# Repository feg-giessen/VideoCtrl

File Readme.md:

# VideoController

Some more photos: https://www.flickr.com/photos/peschuster/tags/videoctrl/

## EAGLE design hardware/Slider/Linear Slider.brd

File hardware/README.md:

# Hardware Files #

- schematics
- part lists
- board layouts

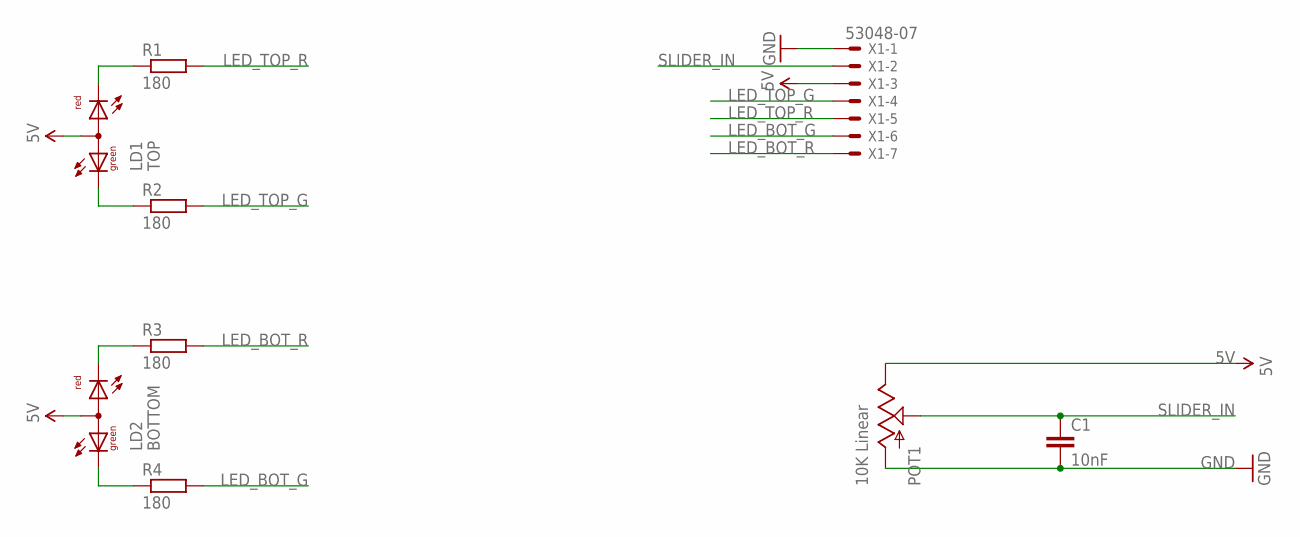
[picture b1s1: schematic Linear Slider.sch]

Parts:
C1: 10nF; 0603-CAP
LD1: TOP; DUOLED-A-5MM
LD2: BOTTOM; DUOLED-A-5MM
POT1: 10K Linear; SLIDER60
R1, R2, R3, R4: 180; R0603
X1: 53048-07

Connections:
5V: LD1.A, LD2.A, POT1.1 (E), X1.3
GND: C1.2, POT1.3 (A), X1.1
LED_BOT_G: R4.2, X1.6
LED_BOT_R: R3.2, X1.7
LED_TOP_G: R2.2, X1.4
LED_TOP_R: R1.2, X1.5
unnamed: LD1.CR, R1.1
unnamed: LD1.CX (CG), R2.1
unnamed: LD2.CX (CG), R4.1
unnamed: LD2.CR, R3.1
SLIDER_IN: C1.1, POT1.2A (S), X1.2

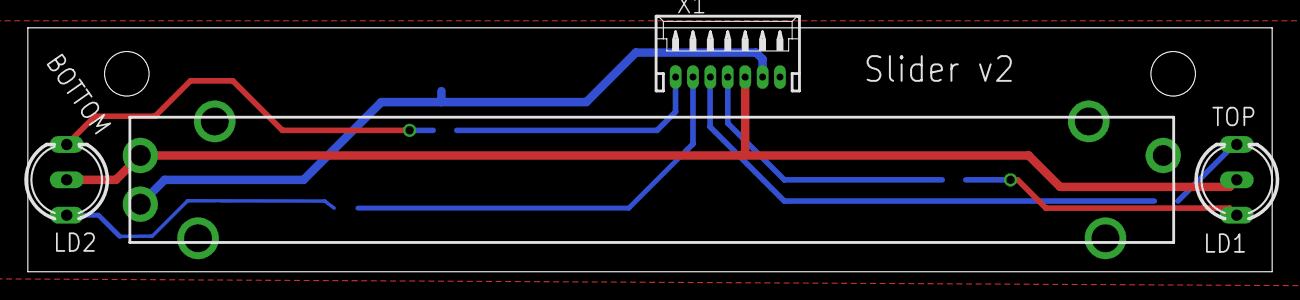
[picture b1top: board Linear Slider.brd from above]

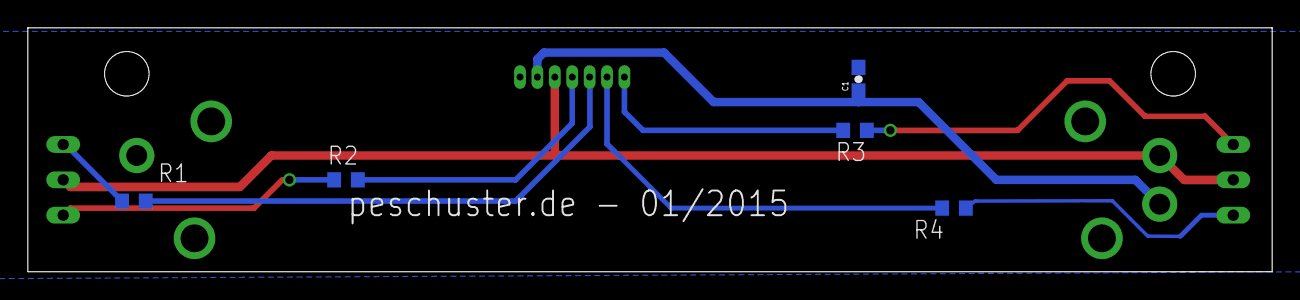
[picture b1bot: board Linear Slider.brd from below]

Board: 2 copper layers, 89.4 x 17.5 mm, 9 parts (5 on the bottom side), 11 nets.

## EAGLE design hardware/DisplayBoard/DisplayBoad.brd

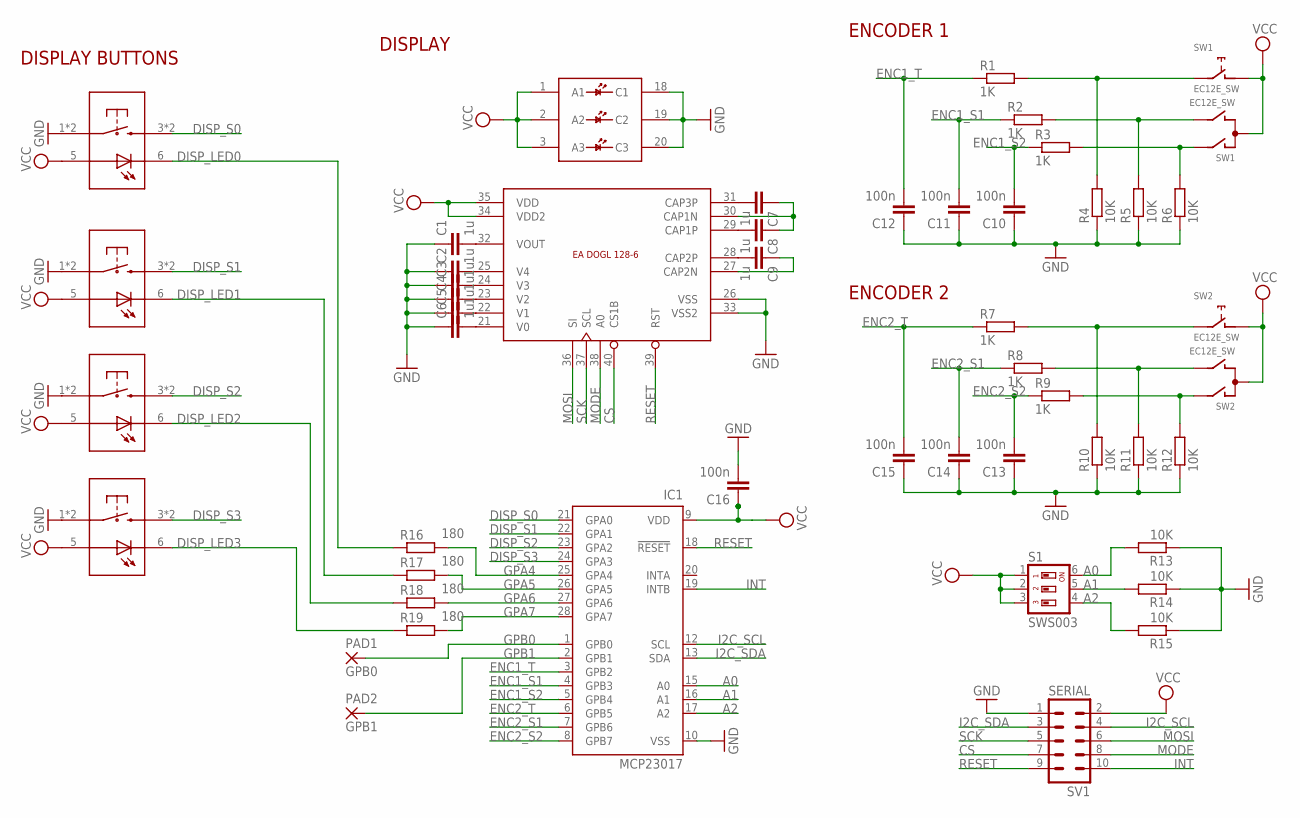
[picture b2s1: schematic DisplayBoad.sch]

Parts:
C1, C2, C3, C4, C5, C6, C7, C8, C9: 1u; C0805
C10, C11, C12, C13, C14, C15, C16: 100n; C0603
IC1: MCP23017; SSOP28
PAD1: GPB0; 2,15/1,0
PAD2: GPB1; 2,15/1,0
R1, R2, R3, R7, R8, R9: 1K; R0603
R4, R5, R6, R10, R11, R12, R13, R14, R15: 10K; R0603
R16, R17, R18, R19: 180; R0603
S1: SWS003; SMS-003
SV1: SERIAL; MA05-2
SW1, SW2: EC12E_SW; ALPS_EC12E_SW
U1: EADOGL128-62; EA_DOGL128-6
U$2, U$3, U$4, U$5: LP15

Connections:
A0: IC1.15 (A0), R13.2, S1.6
A1: IC1.16 (A1), R14.2, S1.5
A2: IC1.17 (A2), R15.2, S1.4
CS: SV1.7, U1.40 (CS1B)
DISP_LED0: R16.1, U$2.6
DISP_LED1: R17.1, U$3.6
DISP_LED2: R18.1, U$4.6
DISP_LED3: R19.1, U$5.6
DISP_S0: IC1.21 (GPA0), U$2.3, U$2.4 (3)
DISP_S1: IC1.22 (GPA1), U$3.3, U$3.4 (3)
DISP_S2: IC1.23 (GPA2), U$4.3, U$4.4 (3)
DISP_S3: IC1.24 (GPA3), U$5.3, U$5.4 (3)
ENC1_S1: C11.2, IC1.4 (GPB3), R2.1
ENC1_S2: C10.2, IC1.5 (GPB4), R3.1
ENC1_T: C12.2, IC1.3 (GPB2), R1.1
ENC2_S1: C14.2, IC1.7 (GPB6), R8.1
ENC2_S2: C13.2, IC1.8 (GPB7), R9.1
ENC2_T: C15.2, IC1.6 (GPB5), R7.1
GND: C1.1, C2.1, C3.1, C4.1, C5.1, C6.1, C10.1, C11.1, C12.1, C13.1, C14.1, C15.1, C16.2, IC1.10 (VSS), R4.1, R5.1, R6.1, R10.1, R11.1, R12.1, R13.1, R14.1, R15.1, SV1.1, U1.18 (C1), U1.19 (C2), U1.20 (C3), U1.26 (VSS), U1.33 (VSS2), U$2.1, U$2.2 (1), U$3.1, U$3.2 (1), U$4.1, U$4.2 (1), U$5.1, U$5.2 (1)
GPA4: IC1.25 (GPA4), R16.2
GPA5: IC1.26 (GPA5), R17.2
GPA6: IC1.27 (GPA6), R18.2
GPA7: IC1.28 (GPA7), R19.2
GPB0: IC1.1 (GPB0), PAD1.1
GPB1: IC1.2 (GPB1), PAD2.1
I2C_SCL: IC1.12 (SCL), SV1.4
I2C_SDA: IC1.13 (SDA), SV1.3
INT: IC1.19 (INTB), SV1.10
MODE: SV1.8, U1.38 (A0)
MOSI: SV1.6, U1.36 (SI)
unnamed: C1.2, U1.32 (VOUT)
unnamed: C2.2, U1.25 (V4)
unnamed: C3.2, U1.24 (V3)
unnamed: C4.2, U1.23 (V2)
unnamed: C5.2, U1.22 (V1)
unnamed: C6.2, U1.21 (V0)
unnamed: C7.2, U1.31 (CAP3P)
unnamed: C8.2, U1.29 (CAP1P)
unnamed: C9.2, U1.28 (CAP2P)
unnamed: C9.1, U1.27 (CAP2N)
unnamed: C7.1, C8.1, U1.30 (CAP1N)
unnamed: R7.2, R10.2, SW2.E (2)
unnamed: R8.2, R11.2, SW2.B
unnamed: R9.2, R12.2, SW2.A
unnamed: R1.2, R4.2, SW1.E (2)
unnamed: R2.2, R5.2, SW1.B
unnamed: R3.2, R6.2, SW1.A
RESET: IC1.18 (!RESET), SV1.9, U1.39 (RST)
SCK: SV1.5, U1.37 (SCL)
VCC: C16.1, IC1.9 (VDD), S1.1, S1.2, S1.3, SV1.2, SW1.C, SW1.D (1), SW2.C, SW2.D (1), U1.1 (A1), U1.2 (A2), U1.3 (A3), U1.34 (VDD2), U1.35 (VDD), U$2.5, U$3.5, U$4.5, U$5.5

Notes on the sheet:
ENCODER 1
ENCODER 2
DISPLAY BUTTONS
DISPLAY

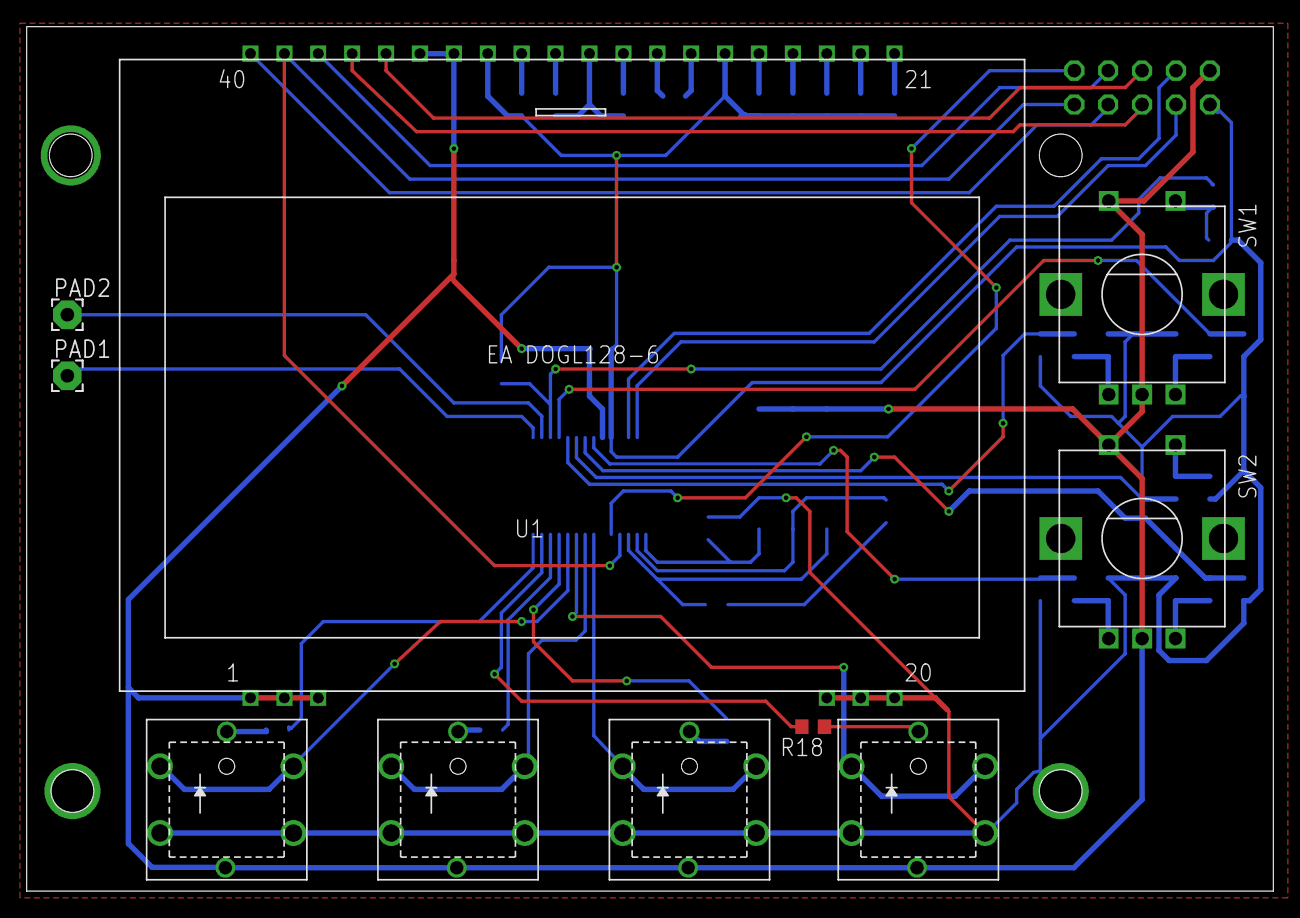
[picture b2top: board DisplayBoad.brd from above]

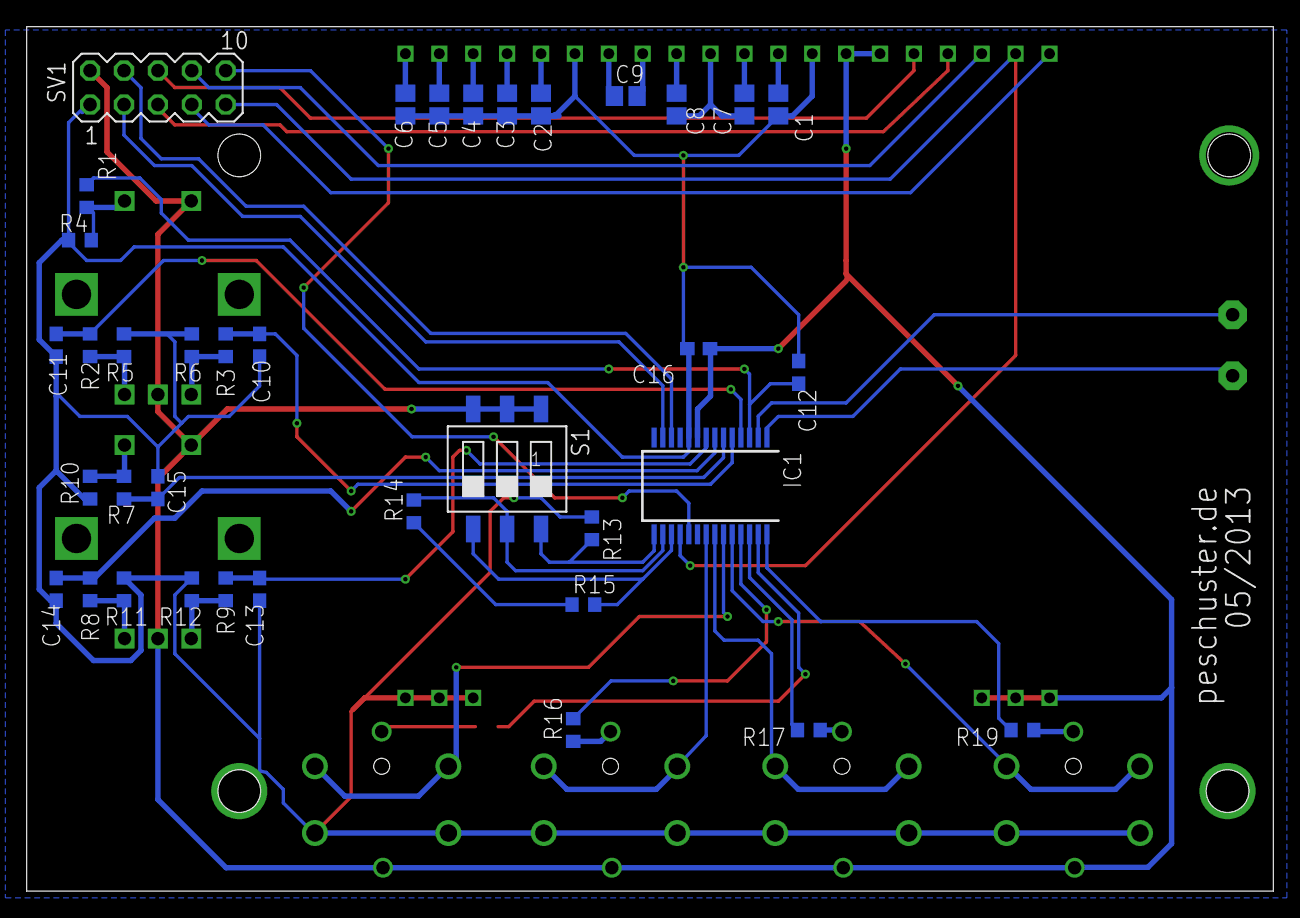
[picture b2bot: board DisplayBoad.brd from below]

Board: 2 copper layers, 93.4 x 64.8 mm, 47 parts (37 on the bottom side), 50 nets.

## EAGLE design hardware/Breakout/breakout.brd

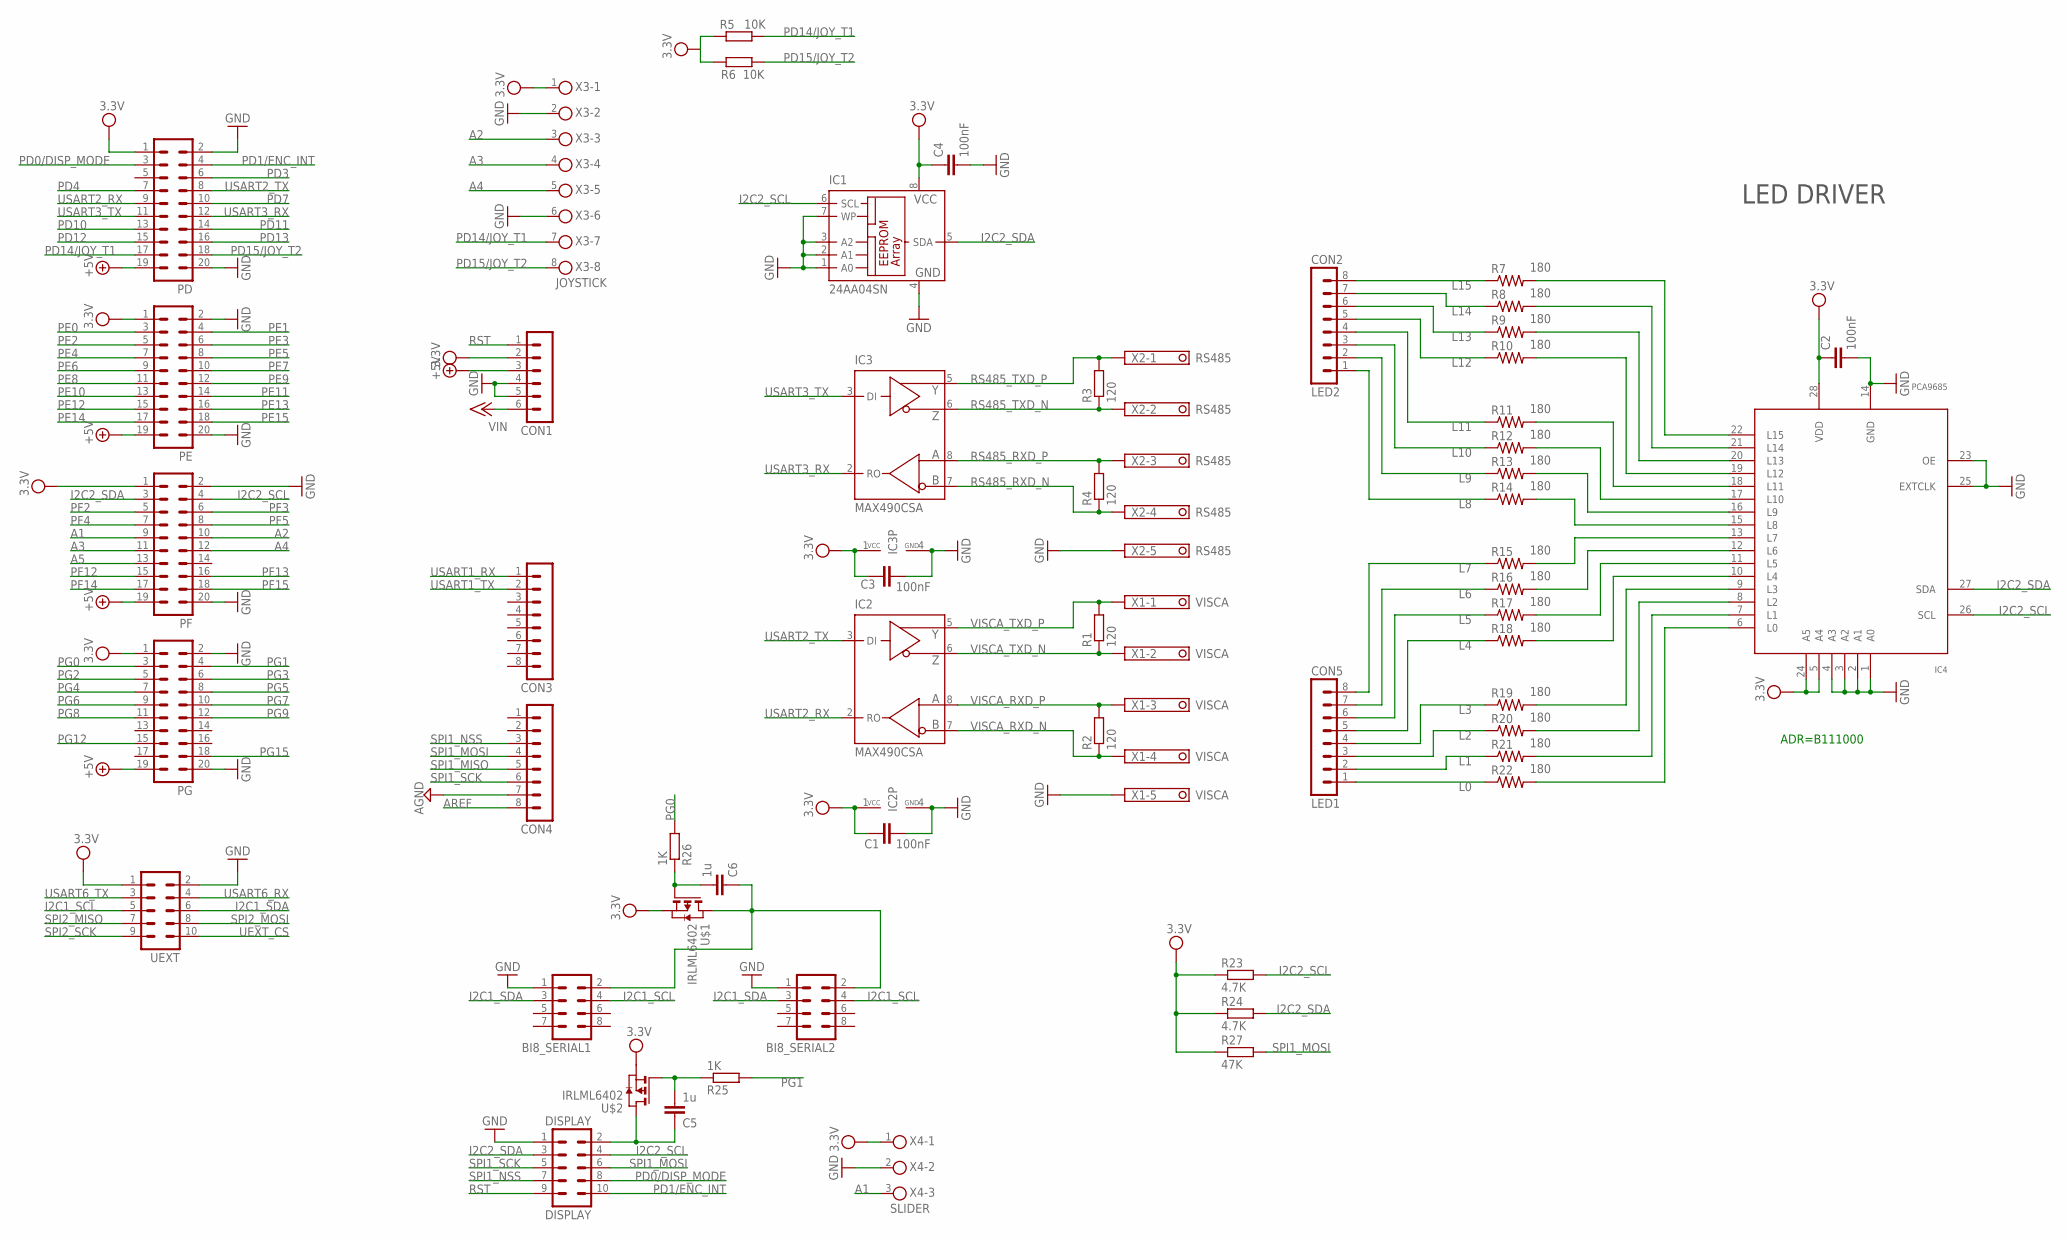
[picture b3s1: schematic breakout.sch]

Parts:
BI8_SERIAL1, BI8_SERIAL2: MA04-2
C1, C2, C3, C4: 100nF; 0603-CAP
C5, C6: 1u; C0805
CON1: MA06-1
CON2: LED2; MA08-1
CON3, CON4: MA08-1
CON5: LED1; MA08-1
DISPLAY: DISPLAY; MA05-2
IC1: 24AA04SN; SO-08
IC2, IC3: MAX490CSA; SO08
IC4: PCA9685; TSSOP28
PD: MA10-2
PE: MA10-2
PF: MA10-2
PG: MA10-2
R1, R2, R3, R4: 120; R0603
R5, R6: 10K; R0603
R7, R8, R9, R10, R11, R12, R13, R14, R15, R16, R17, R18, R19, R20, R21, R22: 180; 0603-RES
R23, R24: 4.7K; R0603
R25, R26: 1K; R0603
R27: 47K; R0603
U$1, U$2: IRLML6402; SOT-23
UEXT: ML10L
X1: VISCA; 1751277
X2: RS485; 1751277
X3: JOYSTICK; 8POL35
X4: SLIDER; 3POL35

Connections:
+5V: CON1.3, PD.19, PE.19, PF.19, PG.19
A1: PF.9, X4.3
A2: PF.10, X3.3
A3: PF.11, X3.4
A4: PF.12, X3.5
A5: PF.13
AGND: CON4.7
AREF: CON4.8
GND: BI8_SERIAL1.1, BI8_SERIAL2.1, C1.2, C2.2, C3.2, C4.2, CON1.4, CON1.5, DISPLAY.1, IC1.1 (A0), IC1.2 (A1), IC1.3 (A2), IC1.4 (GND), IC1.7 (WP), IC2.4 (GND), IC3.4 (GND), IC4.1 (A0), IC4.2 (A1), IC4.3 (A2), IC4.4 (A3), IC4.14 (GND), IC4.23 (OE), IC4.25 (EXTCLK), PD.2, PD.20, PE.2, PE.20, PF.2, PF.20, PG.2, PG.20, UEXT.2, X1.5, X2.5, X3.2, X3.6, X4.2
I2C1_SCL: BI8_SERIAL1.4, BI8_SERIAL2.4, UEXT.5
I2C1_SDA: BI8_SERIAL1.3, BI8_SERIAL2.3, UEXT.6
I2C2_SCL: DISPLAY.4, IC1.6 (SCL), IC4.26 (SCL), PF.4, R23.2
I2C2_SDA: DISPLAY.3, IC1.5 (SDA), IC4.27 (SDA), PF.3, R24.2
L0: CON5.1, R22.1
L1: CON5.2, R21.1
L2: CON5.3, R20.1
L3: CON5.4, R19.1
L4: CON5.5, R18.1
L5: CON5.6, R17.1
L6: CON5.7, R16.1
L7: CON5.8, R15.1
L8: CON2.1, R14.1
L9: CON2.2, R13.1
L10: CON2.3, R12.1
L11: CON2.4, R11.1
L12: CON2.5, R10.1
L13: CON2.6, R9.1
L14: CON2.7, R8.1
L15: CON2.8, R7.1
unnamed: C5.2, R25.1, U$2.1 (G)
unnamed: IC4.13 (L7), R15.2
unnamed: IC4.12 (L6), R16.2
unnamed: C6.2, R26.1, U$1.1 (G)
unnamed: IC4.11 (L5), R17.2
unnamed: BI8_SERIAL1.2, BI8_SERIAL2.2, C6.1, U$1.3 (D)
unnamed: IC4.10 (L4), R18.2
unnamed: IC4.9 (L3), R19.2
unnamed: IC4.8 (L2), R20.2
unnamed: IC4.7 (L1), R21.2
unnamed: C5.1, DISPLAY.2, U$2.3 (D)
unnamed: IC4.6 (L0), R22.2
unnamed: IC4.15 (L8), R14.2
unnamed: IC4.16 (L9), R13.2
unnamed: IC4.17 (L10), R12.2
unnamed: IC4.18 (L11), R11.2
unnamed: IC4.19 (L12), R10.2
unnamed: IC4.20 (L13), R9.2
unnamed: IC4.21 (L14), R8.2
unnamed: IC4.22 (L15), R7.2
PD0/DISP_MODE: DISPLAY.8, PD.3
PD1/ENC_INT: DISPLAY.10, PD.4
PD3: PD.6
PD4: PD.7
PD7: PD.10
PD10: PD.13
PD11: PD.14
PD12: PD.15
PD13: PD.16
PD14/JOY_T1: PD.17, R5.2, X3.7
PD15/JOY_T2: PD.18, R6.2, X3.8
PE0: PE.3
PE1: PE.4
PE2: PE.5
PE3: PE.6
PE4: PE.7
PE5: PE.8
PE6: PE.9
PE7: PE.10
PE8: PE.11
PE9: PE.12
PE10: PE.13
PE11: PE.14
PE12: PE.15
PE13: PE.16
PE14: PE.17
PE15: PE.18
PF2: PF.5
PF3: PF.6
PF4: PF.7
PF5: PF.8
PF12: PF.15
PF13: PF.16
PF14: PF.17
PF15: PF.18
PG0: PG.3, R26.2
PG1: PG.4, R25.2
PG2: PG.5
PG3: PG.6
PG4: PG.7
PG5: PG.8
PG6: PG.9
PG7: PG.10
PG8: PG.11
PG9: PG.12
PG12: PG.15
PG15: PG.18
RS485_RXD_N: IC3.7 (B), R4.1, X2.4
RS485_RXD_P: IC3.8 (A), R4.2, X2.3
RS485_TXD_N: IC3.6 (Z), R3.1, X2.2
RS485_TXD_P: IC3.5 (Y), R3.2, X2.1
RST: CON1.1, DISPLAY.9
SPI1_MISO: CON4.5
SPI1_MOSI: CON4.4, DISPLAY.6, R27.2
SPI1_NSS: CON4.3, DISPLAY.7
SPI1_SCK: CON4.6, DISPLAY.5
SPI2_MISO: UEXT.7
SPI2_MOSI: UEXT.8
SPI2_SCK: UEXT.9
UEXT_CS: UEXT.10
USART1_RX: CON3.1
USART1_TX: CON3.2
USART2_RX: IC2.2 (RO), PD.9
USART2_TX: IC2.3 (DI), PD.8
USART3_RX: IC3.2 (RO), PD.12
USART3_TX: IC3.3 (DI), PD.11
USART6_RX: UEXT.4
USART6_TX: UEXT.3
VCC: C1.1, C2.1, C3.1, C4.1, CON1.2, IC1.8 (VCC), IC2.1 (VCC), IC3.1 (VCC), IC4.5 (A4), IC4.24 (A5), IC4.28 (VDD), PD.1, PE.1, PF.1, PG.1, R5.1, R6.1, R23.1, R24.1, R27.1, U$1.2 (S), U$2.2 (S), UEXT.1, X3.1, X4.1
VIN: CON1.6
VISCA_RXD_N: IC2.7 (B), R2.1, X1.4
VISCA_RXD_P: IC2.8 (A), R2.2, X1.3
VISCA_TXD_N: IC2.6 (Z), R1.1, X1.2
VISCA_TXD_P: IC2.5 (Y), R1.2, X1.1

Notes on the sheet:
ADR=B111000
LED DRIVER

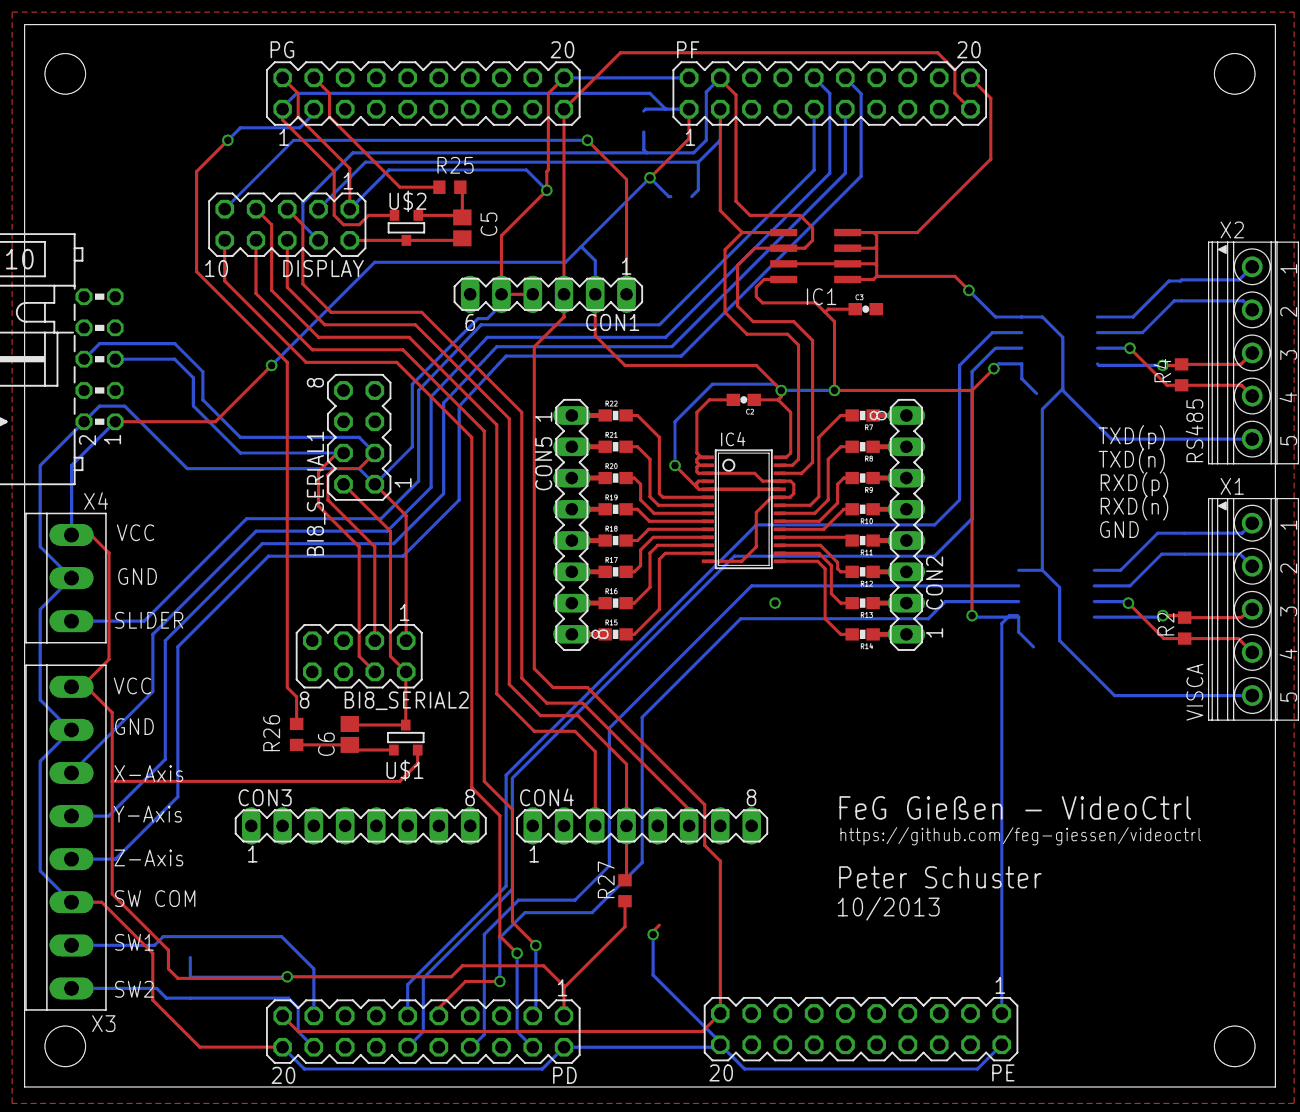
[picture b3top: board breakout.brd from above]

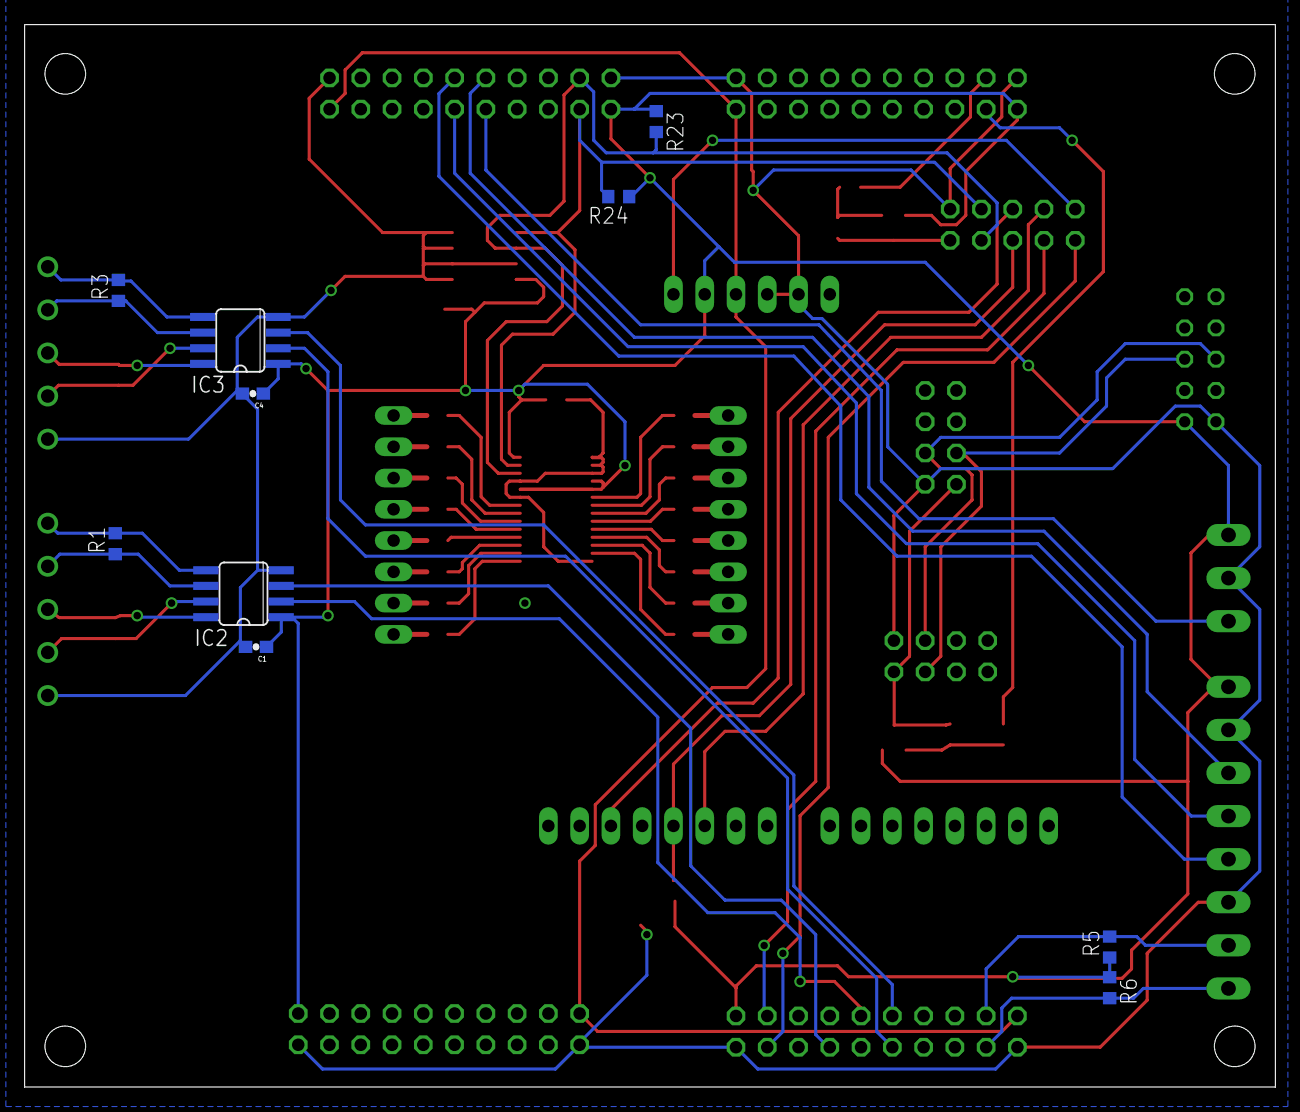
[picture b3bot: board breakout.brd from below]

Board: 2 copper layers, 101.6 x 86.3 mm, 56 parts (10 on the bottom side), 69 nets.

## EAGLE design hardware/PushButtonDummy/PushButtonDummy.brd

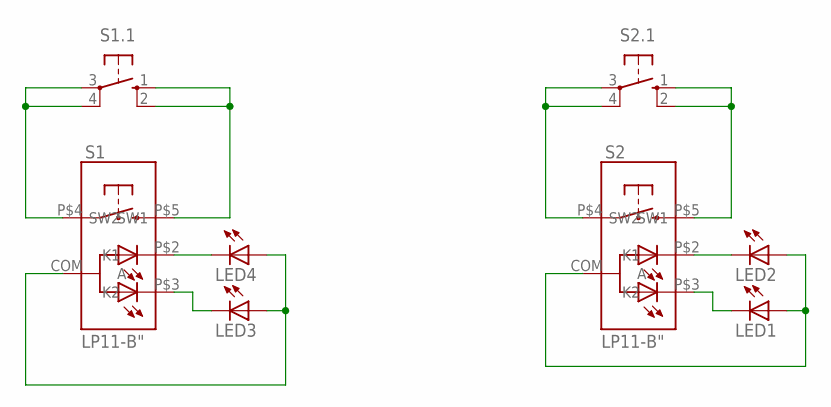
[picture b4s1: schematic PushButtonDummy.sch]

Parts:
LED1, LED2, LED3, LED4: LED3MM
S1, S2: LP11-B"; LP11
S1.1, S2.1: 10-XX; B3F-10XX

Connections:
unnamed: S1.P$4 (SW1), S1.1.3, S1.1.4 (P1)
unnamed: S1.P$5 (SW2), S1.1.1 (S), S1.1.2 (S1)
unnamed: S2.P$5 (SW2), S2.1.1 (S), S2.1.2 (S1)
unnamed: S2.P$4 (SW1), S2.1.3, S2.1.4 (P1)
unnamed: LED4.K (C), S1.P$2 (K1)
unnamed: LED3.K (C), S1.P$3 (K2)
unnamed: LED2.K (C), S2.P$2 (K1)
unnamed: LED1.K (C), S2.P$3 (K2)
unnamed: LED1.A, LED2.A, S2.COM (A)
unnamed: LED3.A, LED4.A, S1.COM (A)

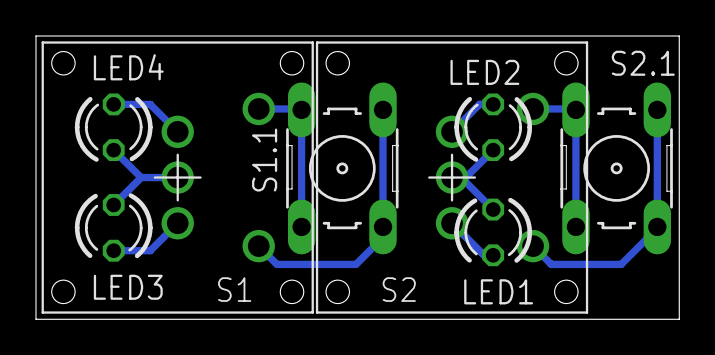
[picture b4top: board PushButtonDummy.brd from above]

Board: 2 copper layers, 35.7 x 15.7 mm, 8 parts (0 on the bottom side), 10 nets.

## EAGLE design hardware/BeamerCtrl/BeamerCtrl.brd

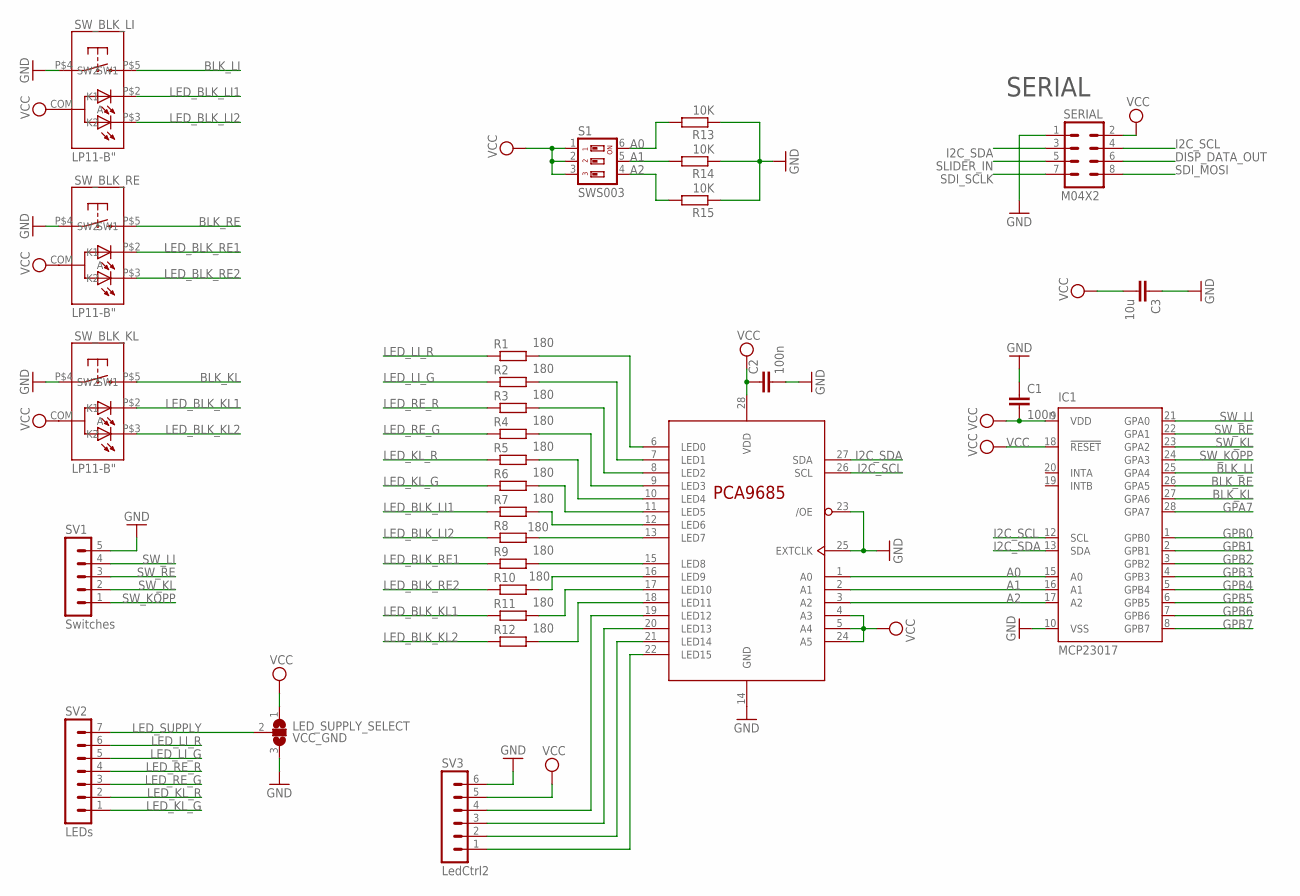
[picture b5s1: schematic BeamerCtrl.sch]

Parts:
C1, C2: 100n; C0603
C3: 10u; C0805
IC1: MCP23017; SSOP28
IC2: PCA9685PW; TSSOP28
LED_SUPPLY_SELECT: VCC_GND; SJ_2
R1, R2, R3, R4, R5, R6, R7, R8, R9, R10, R11, R12: 180; R0603
R13, R14, R15: 10K; R0603
S1: SWS003; SMS-003
SERIAL: M04X2; 2X4
SV1: Switches; MA05-1
SV2: LEDs; MA07-1
SV3: LedCtrl2; MA06-1
SW_BLK_KL: LP11-B"; LP11
SW_BLK_LI: LP11-B"; LP11
SW_BLK_RE: LP11-B"; LP11

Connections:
A0: IC1.15 (A0), IC2.1 (A0), R13.2, S1.6
A1: IC1.16 (A1), IC2.2 (A1), R14.2, S1.5
A2: IC1.17 (A2), IC2.3 (A2), R15.2, S1.4
BLK_KL: IC1.27 (GPA6), SW_BLK_KL.P$5 (SW2)
BLK_LI: IC1.25 (GPA4), SW_BLK_LI.P$5 (SW2)
BLK_RE: IC1.26 (GPA5), SW_BLK_RE.P$5 (SW2)
DISP_DATA_OUT: SERIAL.6
GND: C1.1, C2.2, C3.1, IC1.10 (VSS), IC2.14 (GND), IC2.23 (/OE), IC2.25 (EXTCLK), LED_SUPPLY_SELECT.3, R13.1, R14.1, R15.1, SERIAL.1, SV1.5, SV3.6, SW_BLK_KL.P$4 (SW1), SW_BLK_LI.P$4 (SW1), SW_BLK_RE.P$4 (SW1)
GPA7: IC1.28 (GPA7)
GPB0: IC1.1 (GPB0)
GPB1: IC1.2 (GPB1)
GPB2: IC1.3 (GPB2)
GPB3: IC1.4 (GPB3)
GPB4: IC1.5 (GPB4)
GPB5: IC1.6 (GPB5)
GPB6: IC1.7 (GPB6)
GPB7: IC1.8 (GPB7)
I2C_SCL: IC1.12 (SCL), IC2.26 (SCL), SERIAL.4
I2C_SDA: IC1.13 (SDA), IC2.27 (SDA), SERIAL.3
LED_BLK_KL1: R11.1, SW_BLK_KL.P$2 (K1)
LED_BLK_KL2: R12.1, SW_BLK_KL.P$3 (K2)
LED_BLK_LI1: R7.1, SW_BLK_LI.P$2 (K1)
LED_BLK_LI2: R8.1, SW_BLK_LI.P$3 (K2)
LED_BLK_RE1: R9.1, SW_BLK_RE.P$2 (K1)
LED_BLK_RE2: R10.1, SW_BLK_RE.P$3 (K2)
LED_KL_G: R6.1, SV2.1
LED_KL_R: R5.1, SV2.2
LED_LI_G: R2.1, SV2.5
LED_LI_R: R1.1, SV2.6
LED_RE_G: R4.1, SV2.3
LED_RE_R: R3.1, SV2.4
LED_SUPPLY: LED_SUPPLY_SELECT.2, SV2.7
unnamed: IC2.19 (LED12), SV3.4
unnamed: IC2.20 (LED13), SV3.3
unnamed: IC2.21 (LED14), SV3.2
unnamed: IC2.22 (LED15), SV3.1
unnamed: IC2.6 (LED0), R1.2
unnamed: IC2.7 (LED1), R2.2
unnamed: IC2.8 (LED2), R3.2
unnamed: IC2.9 (LED3), R4.2
unnamed: IC2.10 (LED4), R5.2
unnamed: IC2.11 (LED5), R6.2
unnamed: IC2.12 (LED6), R7.2
unnamed: IC2.13 (LED7), R8.2
unnamed: IC2.15 (LED8), R9.2
unnamed: IC2.16 (LED9), R10.2
unnamed: IC2.17 (LED10), R11.2
unnamed: IC2.18 (LED11), R12.2
SDI_MOSI: SERIAL.8
SDI_SCLK: SERIAL.7
SLIDER_IN: SERIAL.5
SW_KL: IC1.23 (GPA2), SV1.2
SW_KOPP: IC1.24 (GPA3), SV1.1
SW_LI: IC1.21 (GPA0), SV1.4
SW_RE: IC1.22 (GPA1), SV1.3
VCC: C1.2, C2.1, C3.2, IC1.9 (VDD), IC1.18 (!RESET), IC2.4 (A3), IC2.5 (A4), IC2.24 (A5), IC2.28 (VDD), LED_SUPPLY_SELECT.1, S1.1, S1.2, S1.3, SERIAL.2, SV3.5, SW_BLK_KL.COM (A), SW_BLK_LI.COM (A), SW_BLK_RE.COM (A)

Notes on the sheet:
SERIAL

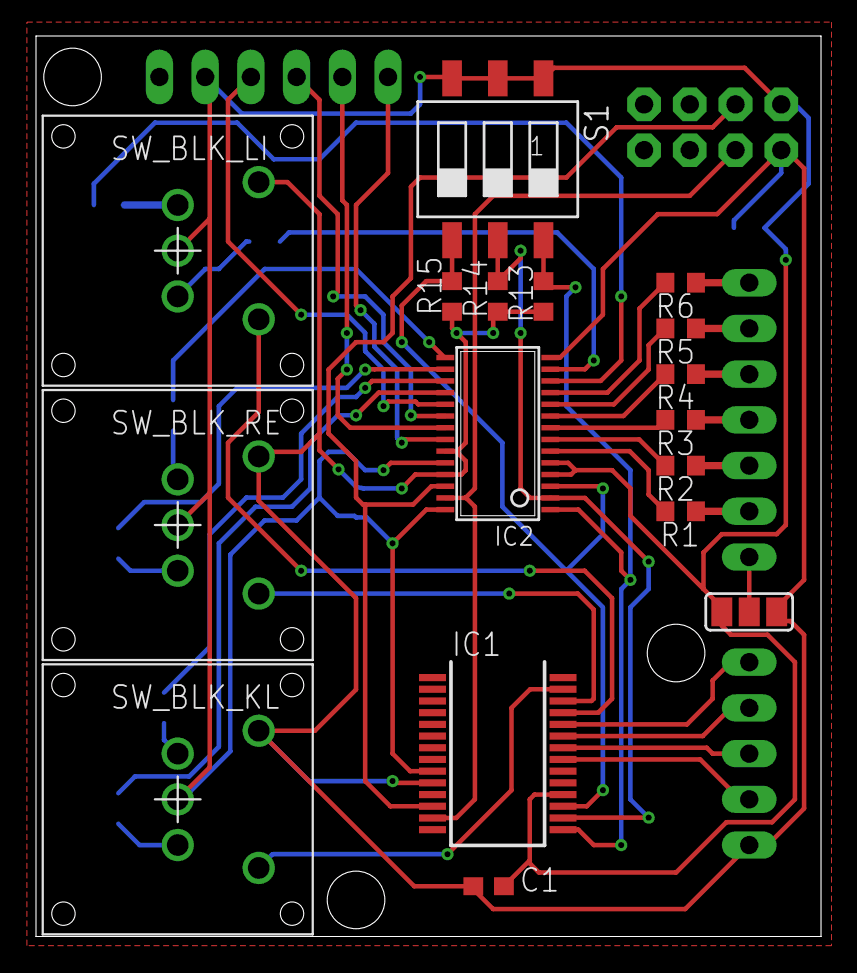
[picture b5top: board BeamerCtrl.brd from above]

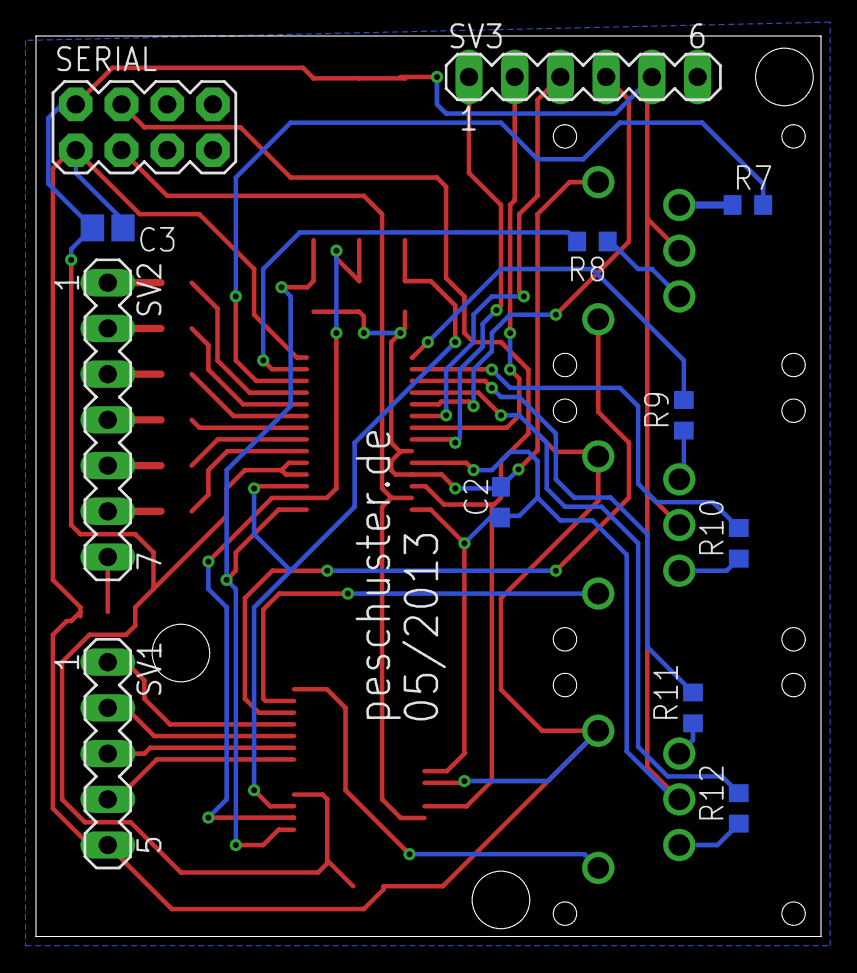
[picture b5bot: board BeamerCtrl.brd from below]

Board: 2 copper layers, 43.6 x 50.0 mm, 29 parts (12 on the bottom side), 43 nets.

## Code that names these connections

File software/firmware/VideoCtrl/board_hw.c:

/*
 * board_hw.c
 *
 *  Created on: 28.10.2013
 *      Author: Peter Schuster
 */

#include "board_hw.h"
#include "debugger.h"

I2CConfig i2c_1_conf;
I2CConfig i2c_2_conf;

SPIConfig spi_1_conf;

static adcsample_t* global_adc_buffer;

/*
 * ADC streaming callback.
 */
size_t adc3_samples_count = 0;
static void adc_cb(ADCDriver *adcp, adcsample_t *buffer, size_t n) {

  (void)adcp;
  if (global_adc_buffer == buffer) {
      adc3_samples_count = n;
  } else {
      adc3_samples_count += n;
  }
}

static void adc_error_cb(ADCDriver *adcp, adcerror_t err) {

  (void)adcp;
  (void)err;
}

/*
 * ADC conversion group.
 * Mode:        Continuous, 16 samples of 8 channels, SW triggered.
 * Channels:    IN11, IN12, IN11, IN12, IN11, IN12, Sensor, VRef.
 */
static const ADCConversionGroup adcgrp_conf3 = {
  TRUE,                         // Enables the circular buffer mode for the group.
  ADC3_CH_NUM,                  // Number of the analog channels belonging to the conversion group.
  adc_cb,                       // Callback function associated to the group or @p NULL.
  adc_error_cb,                 // Error callback or @p NULL.
  0,                            // CR1
  ADC_CR2_SWSTART,              // CR2
  0,                            // SMPR1 - In this field must be specified the sample times for channels 10...18.
  ADC_SMPR2_SMP_AN4(ADC_SAMPLE_56)
   | ADC_SMPR2_SMP_AN5(ADC_SAMPLE_56)
   | ADC_SMPR2_SMP_AN6(ADC_SAMPLE_56)
   | ADC_SMPR2_SMP_AN7(ADC_SAMPLE_56),  // SMPR2 - In this field must be specified the sample times for channels 0...9.
  ADC_SQR1_NUM_CH(ADC3_CH_NUM), // Conversion group sequence 13...16 + sequence length.
  0,                            // Conversion group sequence 7...12.
  ADC_SQR3_SQ1_N(ADC_CHANNEL_IN4)
   | ADC_SQR3_SQ2_N(ADC_CHANNEL_IN5)
   | ADC_SQR3_SQ3_N(ADC_CHANNEL_IN6)
   | ADC_SQR3_SQ4_N(ADC_CHANNEL_IN7)   // Conversion group sequence 1...6.
};

#if VISCA_UART
/*
 * This callback is invoked when a transmission buffer has been completely
 * read by the driver.
 */
static void uart2_tx_end(UARTDriver *uartp) {
    (void)uartp;
    // TODO?
}

/*
 * This callback is invoked when a transmission has physically completed.
 */
static void uart2_tx_end_physical(UARTDriver *uartp) {
    (void)uartp;
    // TODO?
}

/*
 * This callback is invoked when a receive buffer has been completely written.
 */
static void uart2_rx_buffer_filled(UARTDriver *uartp) {
    (void)uartp;
    // TODO?
}

/*
 * This callback is invoked when a character is received but the application
 * was not ready to receive it, the character is passed as parameter.
 */
static void uart2_char_rx(UARTDriver *uartp, uint16_t c) {
    (void)uartp;
    (void)c;
    // TODO?
}

/*
 * This callback is invoked on a receive error, the errors mask is passed
 * as parameter.
 */
void uart2_rx_error(UARTDriver *uartp, uartflags_t e) {
    (void)uartp;
    (void)e;
    // TODO?
}

/*
 * UART 2 driver configuration structure.
 */
static UARTConfig uart_conf2 = {
  uart2_tx_end,
  uart2_tx_end_physical,
  uart2_rx_buffer_filled,
  uart2_char_rx,
  uart2_rx_error,
  9600,            // speed
  0,                // CR1
  USART_CR2_STOP1_BITS | USART_CR2_LINEN,  // CR2
  0                 // CR3
};

#else // -> !VISCA_UART
   SerialConfig sd_2_conf;
#endif // end VISCA_UART

#ifdef LWIP_DEBUG
SerialConfig sd_3_conf;
#endif

void init_board_hal(void) {

    //
    // I2C #1 - BI8 boards

    i2c_1_conf.op_mode = OPMODE_I2C;
    i2c_1_conf.duty_cycle = FAST_DUTY_CYCLE_2;
    i2c_1_conf.clock_speed = 400000;

    i2cStart(&I2CD1, &i2c_1_conf);

    palSetPadMode(GPIOB, GPIOB_I2C1_SCL, PAL_MODE_ALTERNATE(4) | PAL_STM32_OTYPE_OPENDRAIN);   /* SCL */
    palSetPadMode(GPIOB, GPIOB_I2C1_SDA, PAL_MODE_ALTERNATE(4) | PAL_STM32_OTYPE_OPENDRAIN);   /* SDA */

    //
    // I2C #2 - Display-Buttons, EEPROM

    i2c_2_conf.op_mode = OPMODE_I2C;
    i2c_2_conf.duty_cycle = FAST_DUTY_CYCLE_2;
    i2c_2_conf.clock_speed = 400000;

    i2cStart(&I2CD2, &i2c_2_conf);

    palSetPadMode(GPIOF, GPIOF_PIN1, PAL_MODE_ALTERNATE(4) | PAL_STM32_OTYPE_OPENDRAIN);   /* SCL */
    palSetPadMode(GPIOF, GPIOF_PIN0, PAL_MODE_ALTERNATE(4) | PAL_STM32_OTYPE_OPENDRAIN);   /* SDA */

    //
    // SPI #1 - Display
    spi_1_conf.end_cb = NULL; 		// Operation complete callback
    spi_1_conf.ssport = GPIOA;		// Chip select line port
    spi_1_conf.sspad = GPIOA_PIN4;	// Chip select line pad number

    /*
     * SPI1 is on APB2 --> PCLK2 (= 59 MHz)
     *   ==> clk = PCLK2 / (2 << BR[2:0]
     *
     * BR2 -> 001 = 1 --> 59 / (2 << 1) == 59 / 4 -> ~14.75 MHz
     */
    spi_1_conf.cr1 = SPI_CR1_BR_0;

    palSetPadMode(GPIOA, GPIOA_PIN5, PAL_MODE_ALTERNATE(5) | PAL_STM32_OSPEED_HIGHEST);       /* SCK  		*/
    palSetPadMode(GPIOB, GPIOB_PIN5, PAL_MODE_ALTERNATE(5) | PAL_STM32_OSPEED_HIGHEST);       /* MOSI 		*/
    palSetPadMode(GPIOA, GPIOA_PIN4, PAL_MODE_OUTPUT_PUSHPULL | PAL_STM32_OSPEED_HIGHEST);    /* NSS  		*/
    palSetPadMode(GPIOD, GPIOD_PIN0, PAL_MODE_OUTPUT_PUSHPULL | PAL_STM32_OSPEED_HIGHEST);    /* DISP_MODE  */

    palSetPad(GPIOA, GPIOA_PIN4);	// set NSS 		 <= 1
    palClearPad(GPIOD, GPIOD_PIN0);	// set DISP_MODE <= 0

    spiStart(&SPID1, &spi_1_conf);

    //
    // USART2 - VISCA

    palSetPadMode(GPIOD, GPIOD_PIN5, PAL_MODE_ALTERNATE(7));   /* USART2_TX */
    palSetPadMode(GPIOD, GPIOD_PIN6, PAL_MODE_ALTERNATE(7));   /* USART2_RX */

#if	VISCA_UART
    uartStart(&UARTD2, &uart_conf2);
#else
    sd_2_conf.speed = 9600;
    sd_2_conf.cr1   = 0;
    sd_2_conf.cr2   = USART_CR2_STOP1_BITS | USART_CR2_LINEN;
    sd_2_conf.cr3   = 0;

    sdStart(&SD2, &sd_2_conf);
#endif

#ifdef LWIP_DEBUG
    //
    // USART3 - DEBUG

    palSetPadMode(GPIOD, GPIOD_PIN8, PAL_MODE_ALTERNATE(7));   /* USART3_TX */
    palSetPadMode(GPIOD, GPIOD_PIN9, PAL_MODE_ALTERNATE(7));   /* USART3_RX */

    sd_3_conf.speed = 115200;
    sd_3_conf.cr1   = 0;
    sd_3_conf.cr2   = USART_CR2_STOP1_BITS | USART_CR2_LINEN;
    sd_3_conf.cr3   = 0;

    sdStart(&SD3, &sd_3_conf);
#endif

    //
    // ADC 3

    palSetPadMode(GPIOF, GPIOF_PIN6, PAL_MODE_INPUT_ANALOG);    // PF6: Slider
    palSetPadMode(GPIOF, GPIOF_PIN7, PAL_MODE_INPUT_ANALOG);    // PF7: Joy-X
    palSetPadMode(GPIOF, GPIOF_PIN8, PAL_MODE_INPUT_ANALOG);    // PF8: Joy-Y
    palSetPadMode(GPIOF, GPIOF_PIN9, PAL_MODE_INPUT_ANALOG);    // PF9: Joy-Z
}

void enable_adc(adcsample_t* buffer) {

    adcStart(&ADCD3, NULL);
    global_adc_buffer = buffer;

    // Start continous adc conversions
    adcStartConversion(&ADCD3, &adcgrp_conf3, buffer, ADC3_SMP_DEPTH);
}

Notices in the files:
parts and their libraries:
SparkFun: Licensing: CC v3.0 Share-Alike You are welcome to use this library for commercial purposes.
